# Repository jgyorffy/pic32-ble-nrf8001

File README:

The motivation of this project was to refactor and target the Nordic code for Arduino to a PIC32. The code-base is event-driven and does rely on an interrupt vs polling.  It is specific to a UART-driven application. The use-case is for pushing bulk data (20-byte packets).

There are two parts to this project:
1. nRF8001 schematic and board (Eagle)
2. PIC 32 focused UART driver

The board uses only 0402 components to reduce mutual inductances so you will need a good magnifying system to lay down the components.  There is a board already created on OSHPark:
https://oshpark.com/shared_projects/0P89EtVt

This can be tested by using Nordic's Android application called BLE-UART. Currently, the driver just sends back what was sent.

***NOTE: Android has a bug in the BLE code and will not refresh the characteristics. Please refer to this fix (hack):

http://stackoverflow.com/questions/22596951/how-to-programmatically-force-bluetooth-low-energy-service-discovery-on-android

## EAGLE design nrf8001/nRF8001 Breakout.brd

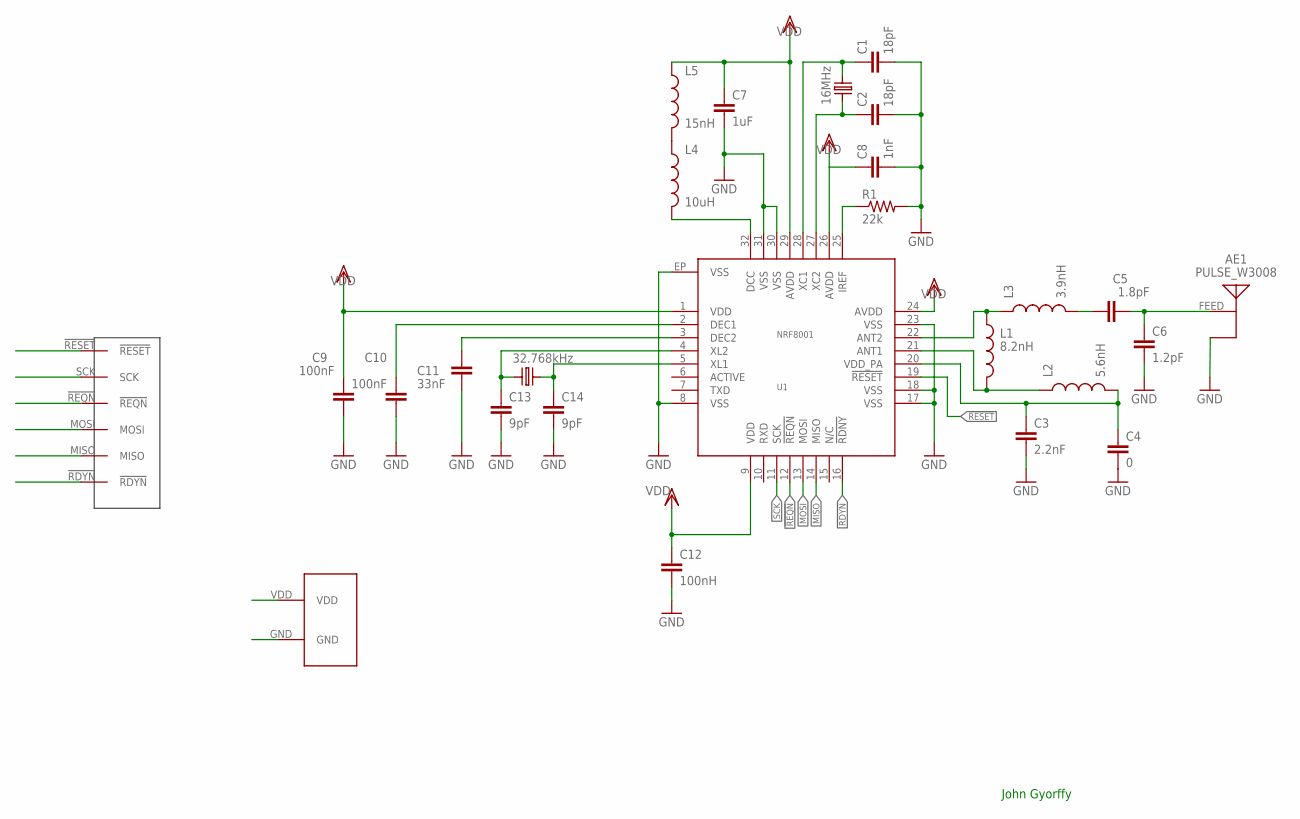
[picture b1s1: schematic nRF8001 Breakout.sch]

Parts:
AE1: PULSE_W3008; MANUFACTURER_PN W3008
C1, C2: 18pF; C0402
C3: 2.2nF; C0402
C4: 0; C0402
C5: 1.8pF; C0402
C6: 1.2pF; C0402
C7: 1uF; C0402
C8: 1nF; C0402
C9, C10: 100nF; C0402
C11: 33nF; C0402
C12: 100nH; C0402
C13, C14: 9pF; C0402
L1: 8.2nH; SPARK_FUN_C0402
L2: 5.6nH; SPARK_FUN_C0402
L3: 3.9nH; SPARK_FUN_C0402
L4: 10uH; SPARK_FUN_C0402
L5: 15nH; SPARK_FUN_C0402
R1: 22k; R0402
U1: NRF8001; QFN-32; MANUFACTURER_PN NRF8001-R2Q32-T
U3: 6_END_CNX; 6_END_BRD_CNX
U$5: 2_END_CNX; 2_END_BRD_CNX
X1: 16MHz; CRYSTAL-2.5X3.5; MANUFACTURER_PN ABM8G-16.000MHZ-B4Y-T
X2: 32.768kHz; CRYSTAL-ABS10; MANUFACTURER_PN ABS10-32.768KHZ-9-T

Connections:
!RDYN: U1.16 (!RDNY), U3.!RDYN
!REQN: U1.12 (!REQN), U3.!REQN
!RESET: U1.19 (!RESET), U3.!RESET
ANT: AE1.FEED, C5.2, C6.1
GND: C1.2, C2.2, C3.2, C4.2, C6.2, C7.2, C8.2, C9.2, C10.2, C11.2, C12.2, C13.2, C14.2, R1.2, U1.8 (VSS), U1.17 (VSS), U1.18 (VSS), U1.23 (VSS), U1.30 (VSS), U1.31 (VSS), U1.EP (VSS), U$5.GND
MISO: U1.14 (MISO), U3.MISO
MOSI: U1.13 (MOSI), U3.MOSI
unnamed: L4.1, L5.2
unnamed: L4.2, U1.32 (DCC)
unnamed: L1.1, L3.1, U1.22 (ANT2)
unnamed: C10.1, U1.2 (DEC1)
unnamed: C11.1, U1.3 (DEC2)
unnamed: L1.2, L2.1, U1.21 (ANT1)
unnamed: C5.1, L3.2
unnamed: R1.1, U1.25 (IREF)
unnamed: C3.1, C4.1, L2.2, U1.20 (VDD_PA)
unnamed: C2.1, U1.27 (XC2), X1.P$1
unnamed: C1.1, U1.28 (XC1), X1.P$3
unnamed: C13.1, U1.4 (XL2), X2.P$2
unnamed: C14.1, U1.5 (XL1), X2.P$1
SCK: U1.11 (SCK), U3.SCK
VDD: C7.1, C8.1, C9.1, C12.1, L5.1, U1.1 (VDD), U1.9 (VDD), U1.24 (AVDD), U1.26 (AVDD), U1.29 (AVDD), U$5.VDD

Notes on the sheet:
John Gyorffy

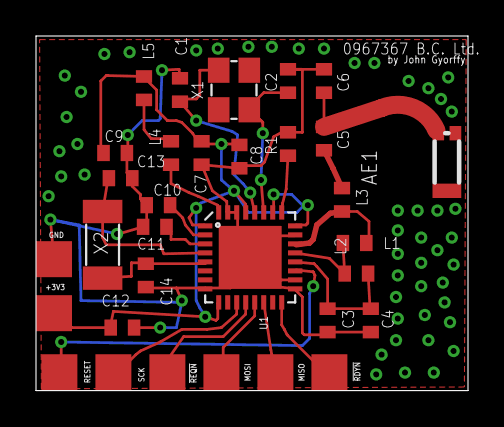
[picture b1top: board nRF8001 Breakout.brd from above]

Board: 2 copper layers, 24.0 x 19.7 mm, 26 parts (0 on the bottom side), 22 nets.

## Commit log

2015-02-08 First revision
2015-02-08 Added eagle schematic and board
2015-02-08 Added readme file
2015-02-08 Added BOM file
2015-02-08 Delete eagle.epf
    auto generated
2015-02-08 fixed bug in timer and added more queue space
